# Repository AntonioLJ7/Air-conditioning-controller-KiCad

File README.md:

Designing an air conditioning control with KiCad software

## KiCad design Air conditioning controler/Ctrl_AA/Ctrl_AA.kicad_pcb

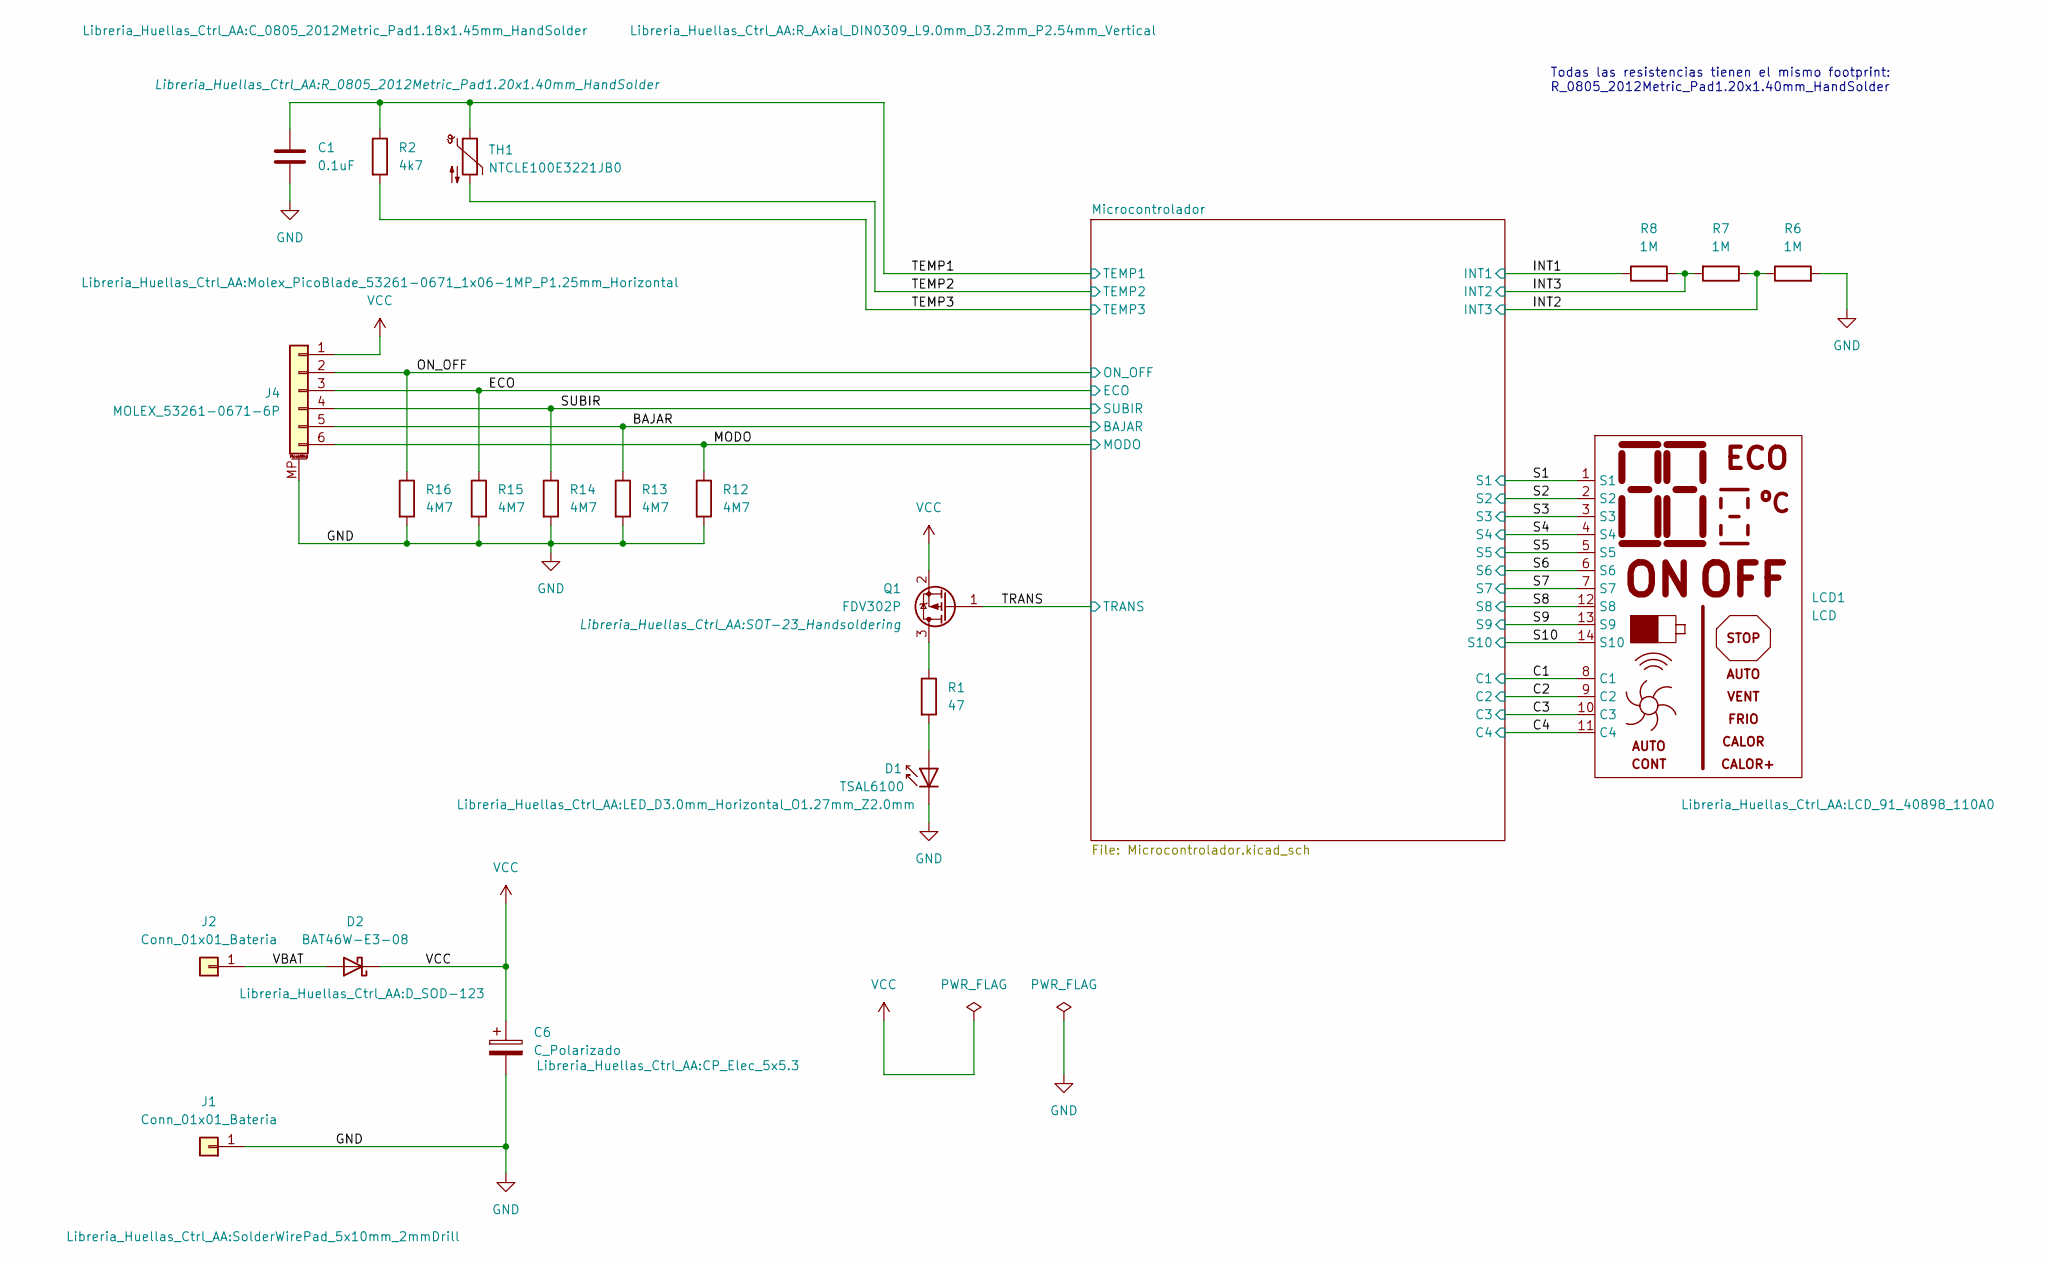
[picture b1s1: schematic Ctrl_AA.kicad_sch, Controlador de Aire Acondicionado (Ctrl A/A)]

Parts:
C1: 0.1uF; C_0805_2012Metric_Pad1.18x1.45mm_HandSolder
C6: C_Polarizado; CP_Elec_5x5.3
D1: TSAL6100; LED_D3.0mm_Horizontal_O1.27mm_Z2.0mm
D2: BAT46W-E3-08; D_SOD-123
J1, J2: Conn_01x01_Bateria; SolderWirePad_5x10mm_2mmDrill
J4: MOLEX_53261-0671-6P; Molex_PicoBlade_53261-0671_1x06-1MP_P1.25mm_Horizontal
LCD1: LCD; LCD_91_40898_110A0
Q1: FDV302P; SOT-23_Handsoldering
R1: 47; R_0805_2012Metric_Pad1.20x1.40mm_HandSolder
R2: 4k7; R_0805_2012Metric_Pad1.20x1.40mm_HandSolder
R6, R7, R8: 1M; R_0805_2012Metric_Pad1.20x1.40mm_HandSolder
R12, R13, R14, R15, R16: 4M7; R_0805_2012Metric_Pad1.20x1.40mm_HandSolder
TH1: NTCLE100E3221JB0; R_Axial_DIN0309_L9.0mm_D3.2mm_P2.54mm_Vertical

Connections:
/BAJAR: J4.5, R13.1; also elsewhere on the board
/C1: LCD1.8 (C1); also elsewhere on the board
/C2: LCD1.9 (C2); also elsewhere on the board
/C3: LCD1.10 (C3); also elsewhere on the board
/C4: LCD1.11 (C4); also elsewhere on the board
/ECO: J4.3, R15.1; also elsewhere on the board
/INT1: R8.1; also elsewhere on the board
/INT2: R6.1, R7.1; also elsewhere on the board
/INT3: R7.2, R8.2; also elsewhere on the board
/MODO: J4.6, R12.1; also elsewhere on the board
/ON_OFF: J4.2, R16.1; also elsewhere on the board
/S1: LCD1.1 (S1); also elsewhere on the board
/S2: LCD1.2 (S2); also elsewhere on the board
/S3: LCD1.3 (S3); also elsewhere on the board
/S4: LCD1.4 (S4); also elsewhere on the board
/S5: LCD1.5 (S5); also elsewhere on the board
/S6: LCD1.6 (S6); also elsewhere on the board
/S7: LCD1.7 (S7); also elsewhere on the board
/S8: LCD1.12 (S8); also elsewhere on the board
/S9: LCD1.13 (S9); also elsewhere on the board
/S10: LCD1.14 (S10); also elsewhere on the board
/SUBIR: J4.4, R14.1; also elsewhere on the board
/TEMP1: C1.1, R2.1, TH1.1; also elsewhere on the board
/TEMP2: TH1.2; also elsewhere on the board
/TEMP3: R2.2; also elsewhere on the board
/TRANS: Q1.1 (G); also elsewhere on the board
/VBAT: D2.2 (A), J2.1
GND: C1.2, C6.2, D1.1 (K), J1.1, J4.MP (MountPin), R6.2, R12.2, R13.2, R14.2, R15.2, R16.2; also elsewhere on the board
unnamed: D1.2 (A), R1.2
unnamed: Q1.3 (D), R1.1
VCC: C6.1, D2.1 (K), J4.1, Q1.2 (S); also elsewhere on the board

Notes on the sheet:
Todas las resistencias tienen el mismo footprint: R_0805_2012Metric_Pad1.20x1.40mm_HandSolder

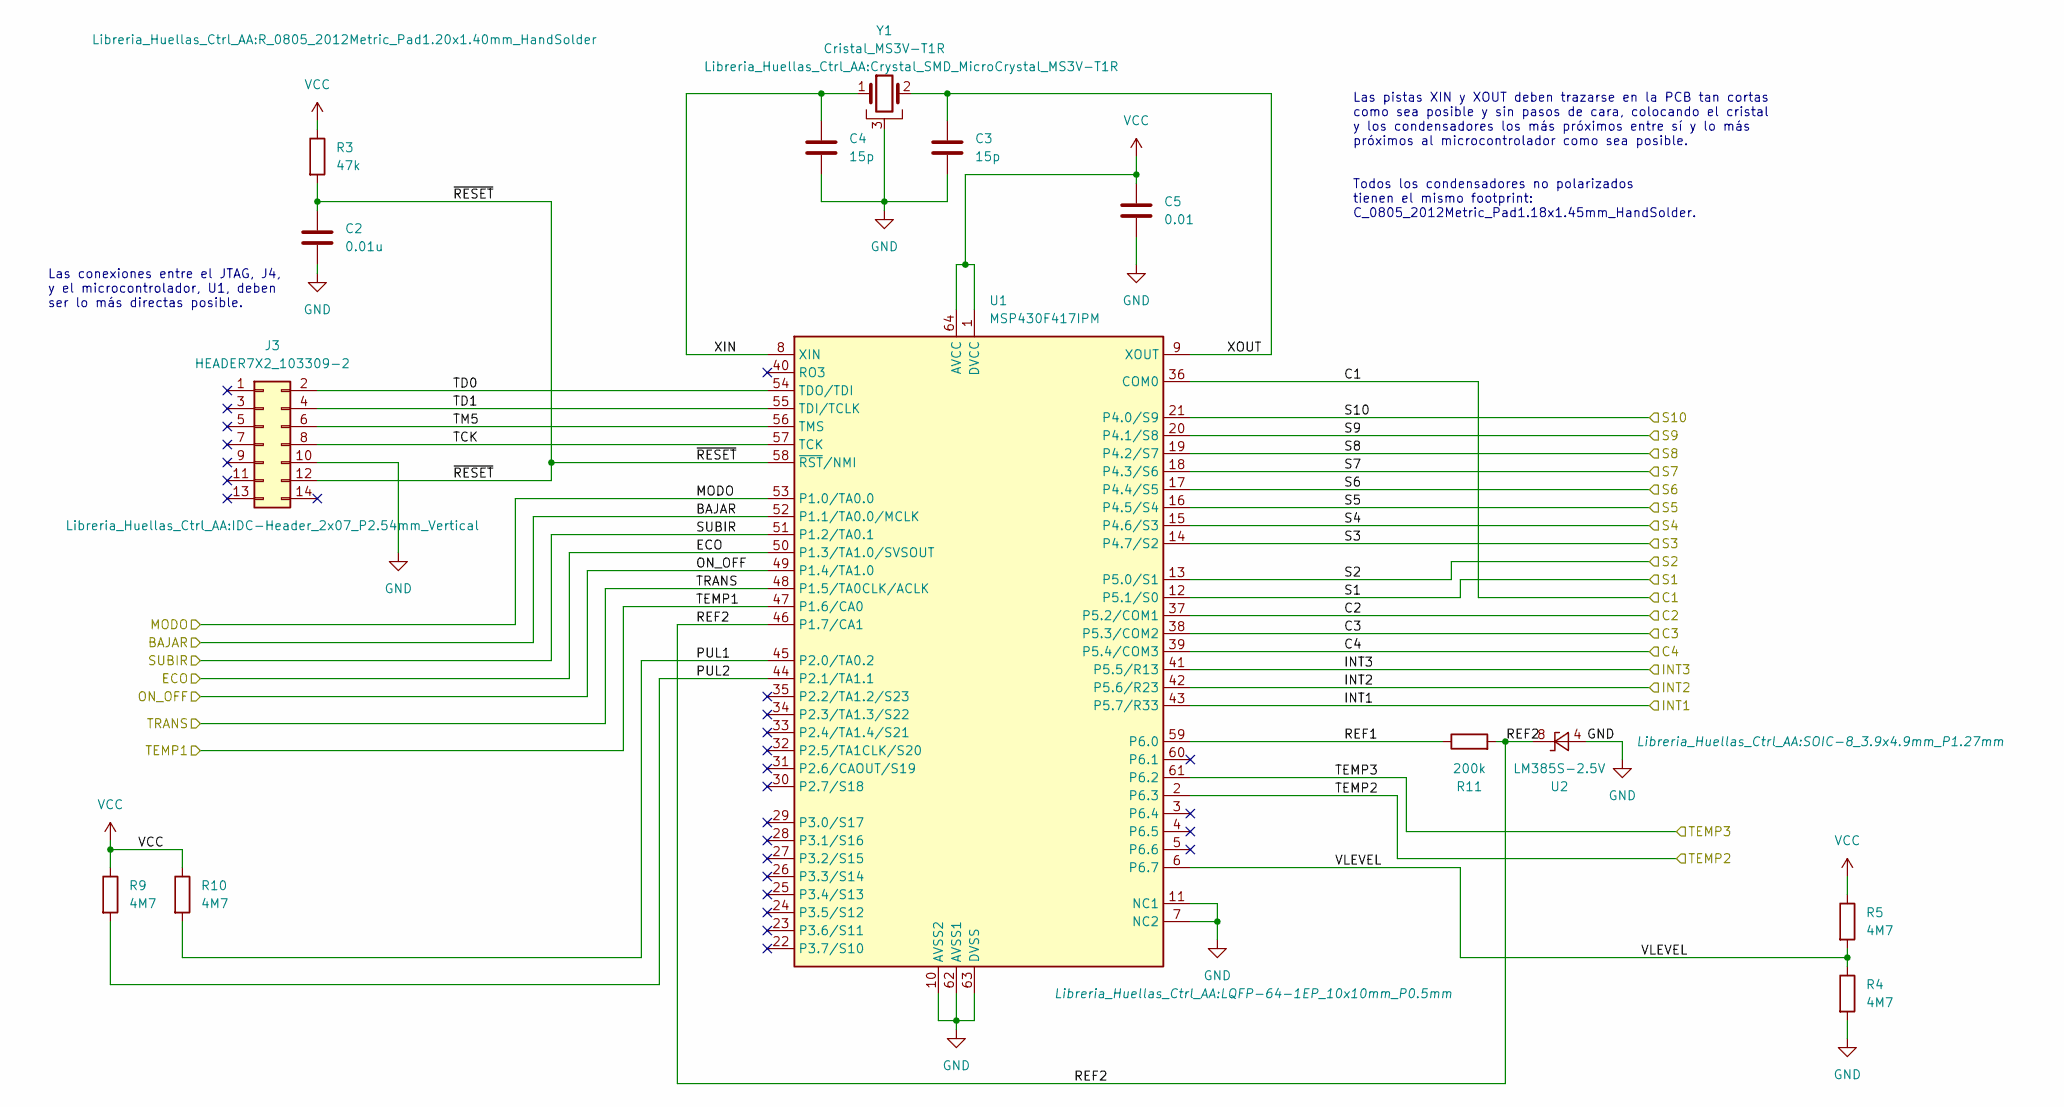
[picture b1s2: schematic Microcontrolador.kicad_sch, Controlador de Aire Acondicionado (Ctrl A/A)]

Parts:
C2: 0.01u; C_0805_2012Metric_Pad1.18x1.45mm_HandSolder
C3, C4: 15p; C_0805_2012Metric_Pad1.18x1.45mm_HandSolder
C5: 0.01; C_0805_2012Metric_Pad1.18x1.45mm_HandSolder
J3: HEADER7X2_103309-2; IDC-Header_2x07_P2.54mm_Vertical
R3: 47k; R_0805_2012Metric_Pad1.20x1.40mm_HandSolder
R4, R5, R9, R10: 4M7; R_0805_2012Metric_Pad1.20x1.40mm_HandSolder
R11: 200k; R_0805_2012Metric_Pad1.20x1.40mm_HandSolder
U1: MSP430F417IPM; LQFP-64-1EP_10x10mm_P0.5mm
U2: LM385S-2.5V; SOIC-8_3.9x4.9mm_P1.27mm
Y1: Cristal_MS3V-T1R; Crystal_SMD_MicroCrystal_MS3V-T1R

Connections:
/BAJAR: U1.52 (P1.1/TA0.0/MCLK); also elsewhere on the board
/C1: U1.36 (COM0); also elsewhere on the board
/C2: U1.37 (P5.2/COM1); also elsewhere on the board
/C3: U1.38 (P5.3/COM2); also elsewhere on the board
/C4: U1.39 (P5.4/COM3); also elsewhere on the board
/ECO: U1.50 (P1.3/TA1.0/SVSOUT); also elsewhere on the board
/INT1: U1.43 (P5.7/R33); also elsewhere on the board
/INT2: U1.41 (P5.5/R13); also elsewhere on the board
/INT3: U1.42 (P5.6/R23); also elsewhere on the board
/MODO: U1.53 (P1.0/TA0.0); also elsewhere on the board
/Microcontrolador/PUL1: R10.2, U1.45 (P2.0/TA0.2)
/Microcontrolador/PUL2: R9.2, U1.44 (P2.1/TA1.1)
/Microcontrolador/REF1: R11.1, U1.59 (P6.0)
/Microcontrolador/REF2: R11.2, U1.46 (P1.7/CA1), U2.6 (K), U2.8 (K)
/Microcontrolador/TCK: J3.8, U1.57 (TCK)
/Microcontrolador/TD0: J3.2, U1.54 (TDO/TDI)
/Microcontrolador/TD1: J3.4, U1.55 (TDI/TCLK)
/Microcontrolador/TM5: J3.6, U1.56 (TMS)
/Microcontrolador/VLEVEL: R4.1, R5.2, U1.6 (P6.7)
/Microcontrolador/XIN: C4.1, U1.8 (XIN), Y1.1
/Microcontrolador/XOUT: C3.1, U1.9 (XOUT), Y1.2
/Microcontrolador/~RESET: C2.1, J3.12, R3.2, U1.58 (~RST/NMI)
/ON_OFF: U1.49 (P1.4/TA1.0); also elsewhere on the board
/S1: U1.12 (P5.1/S0); also elsewhere on the board
/S2: U1.13 (P5.0/S1); also elsewhere on the board
/S3: U1.14 (P4.7/S2); also elsewhere on the board
/S4: U1.15 (P4.6/S3); also elsewhere on the board
/S5: U1.16 (P4.5/S4); also elsewhere on the board
/S6: U1.17 (P4.4/S5); also elsewhere on the board
/S7: U1.18 (P4.3/S6); also elsewhere on the board
/S8: U1.19 (P4.2/S7); also elsewhere on the board
/S9: U1.20 (P4.1/S8); also elsewhere on the board
/S10: U1.21 (P4.0/S9); also elsewhere on the board
/SUBIR: U1.51 (P1.2/TA0.1); also elsewhere on the board
/TEMP1: U1.47 (P1.6/CA0); also elsewhere on the board
/TEMP2: U1.2 (P6.3); also elsewhere on the board
/TEMP3: U1.61 (P6.2); also elsewhere on the board
/TRANS: U1.48 (P1.5/TA0CLK/ACLK); also elsewhere on the board
GND: C2.2, C3.2, C4.2, C5.2, J3.10, R4.2, U1.7 (NC2), U1.10 (AVSS2), U1.11 (NC1), U1.62 (AVSS1), U1.63 (DVSS), U2.4 (A), Y1.3; also elsewhere on the board
VCC: C5.1, R3.1, R5.1, R9.1, R10.1, U1.1 (DVCC), U1.64 (AVCC); also elsewhere on the board

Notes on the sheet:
Las pistas XIN y XOUT deben trazarse en la PCB tan cortas como sea posible y sin pasos de cara, colocando el cristal y los condensadores los más próximos entre sí y lo más próximos al microcontrolador como sea posible.
Todos los condensadores no polarizados tienen el mismo footprint: C_0805_2012Metric_Pad1.18x1.45mm_HandSolder.
Las conexiones entre el JTAG, J4, y el microcontrolador, U1, deben ser lo más directas posible.

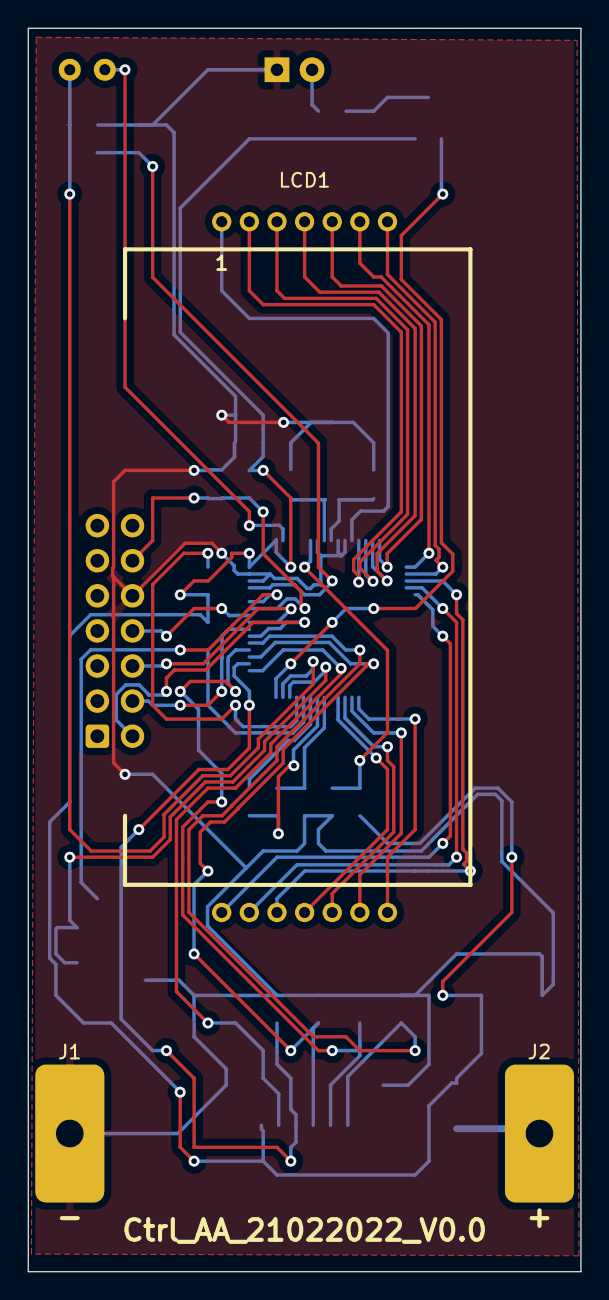
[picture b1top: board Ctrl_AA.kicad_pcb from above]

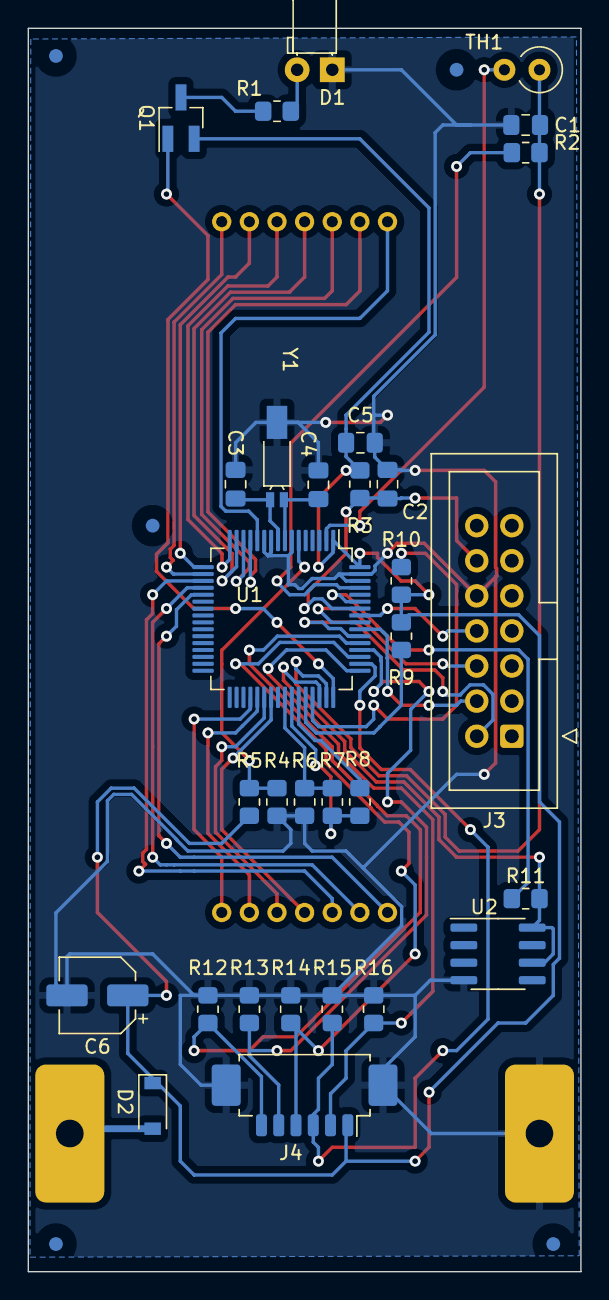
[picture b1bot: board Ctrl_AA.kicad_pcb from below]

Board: 2 copper layers, 40.0 x 90.0 mm, 34 parts (31 on the bottom side), 43 nets.
